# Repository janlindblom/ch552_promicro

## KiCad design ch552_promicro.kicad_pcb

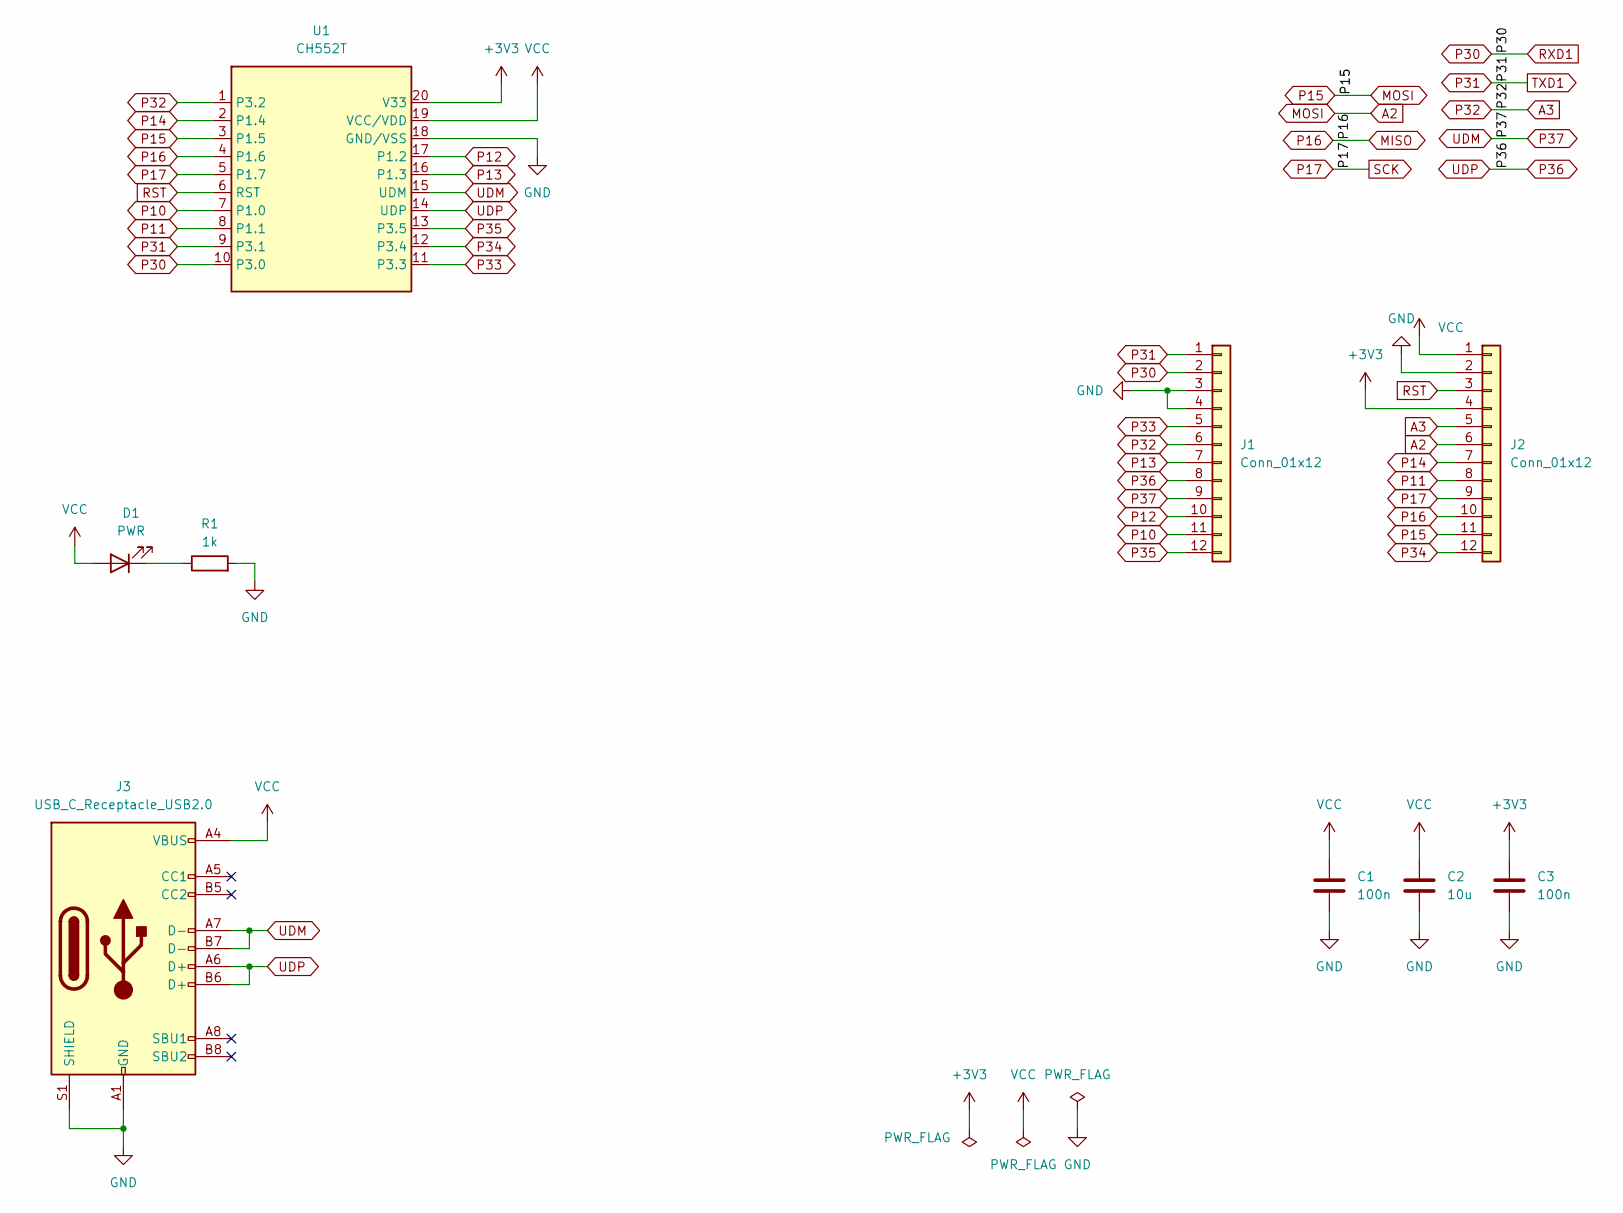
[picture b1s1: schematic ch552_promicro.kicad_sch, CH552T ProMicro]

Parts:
C1, C3: 100n; C_0805_2012Metric_Pad1.18x1.45mm_HandSolder
C2: 10u; C_0805_2012Metric_Pad1.18x1.45mm_HandSolder
D1: PWR; LED_1206_3216Metric_Pad1.42x1.75mm_HandSolder
J1, J2: Conn_01x12; PinHeader_1x12_P2.54mm_Vertical
J3: USB_C_Receptacle_USB2.0; USB_C_Receptacle_Palconn_UTC16-G
R1: 1k; R_0805_2012Metric_Pad1.20x1.40mm_HandSolder
U1: CH552T; TSSOP-20_4.4x6.5mm_P0.65mm

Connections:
+3V3: C3.1, J2.4, U1.20 (V33)
A2: J2.6, J2.11, U1.3 (P1.5)
A3: J1.6, J2.5, U1.1 (P3.2)
GND: C1.2, C2.2, C3.2, J1.3, J1.4, J2.2, J3.A1 (GND), J3.A12 (GND), J3.B1 (GND), J3.B12 (GND), J3.S1 (SHIELD), R1.2, U1.18 (GND/VSS)
MISO: J2.10, U1.4 (P1.6)
unnamed: D1.1 (K), R1.1
P10: J1.11, U1.7 (P1.0)
P11: J2.8, U1.8 (P1.1)
P12: J1.10, U1.17 (P1.2)
P13: J1.7, U1.16 (P1.3)
P14: J2.7, U1.2 (P1.4)
P17: J2.9, U1.5 (P1.7)
P30: J1.2, U1.10 (P3.0)
P31: J1.1, U1.9 (P3.1)
P33: J1.5, U1.11 (P3.3)
P34: J2.12, U1.12 (P3.4)
P35: J1.12, U1.13 (P3.5)
P36: J1.8, J3.A6 (D+), J3.B6 (D+), U1.14 (UDP)
P37: J1.9, J3.A7 (D-), J3.B7 (D-), U1.15 (UDM)
RST: J2.3, U1.6 (RST)
VCC: C1.1, C2.1, D1.2 (A), J2.1, J3.A4 (VBUS), J3.A9 (VBUS), J3.B4 (VBUS), J3.B9 (VBUS), U1.19 (VCC/VDD)

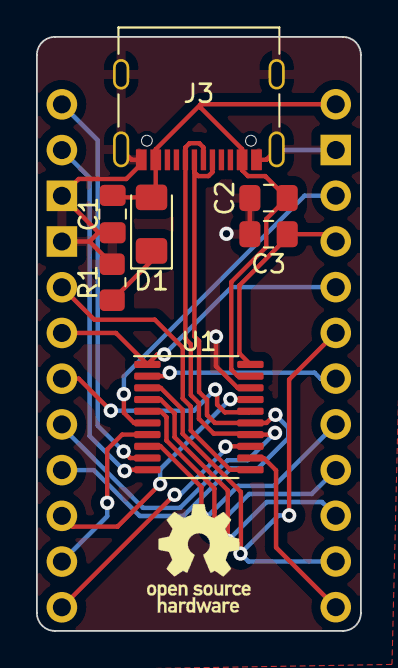
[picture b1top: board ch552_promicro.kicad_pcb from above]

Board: 2 copper layers, 18.0 x 33.0 mm, 9 parts (0 on the bottom side), 21 nets.

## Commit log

2023-10-20 Initial commit of the ProMicro footprint CH552T microcontroller board.
2023-10-20 Make sure it's open source.
2023-10-21 Preparing a README.
